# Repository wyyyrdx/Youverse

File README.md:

# 🌌 Youverse

> **You are here. Your habits shape the possibilities.**

### Built for Reverie Hacks 2026

Youverse is a behavioral simulation platform that explores how your current habits and environment can influence different possible versions of your future self.

Instead of telling you what your future will be, Youverse helps you understand how your **current state can shape future possibilities**.

[🎥 Watch the Demo](https://youtu.be/ZdHFRG2crXw?si=tzGFYWxcKCb7MCAu)

---

## 📖 Contents

- [🧠 The Idea](#-the-idea)
- [✨ Why Youverse?](#-why-youverse)
- [🔮 How It Works](#-how-it-works)
- [🪐 The Future Selves](#-the-future-selves)
- [🎮 What-If Simulation](#-what-if-simulation)
- [🏗️ System Architecture](#️-system-architecture)
- [🛠️ Tech Stack](#️-tech-stack)
- [📁 Repository Structure](#-repository-structure)
- [🚀 How to run the project](#-How-to-run-the-project)
- [📊 Data Flow](#-data-flow)
- [🔬 Scientific Honesty](#-scientific-honesty)
- [🧪 Current Status](#-current-status)
- [🌱 Future Vision](#-future-vision)
- [👥 Team](#-team)

---

## 🧠 The Idea

We often think about the future as a single destination.

But the future is shaped by what we repeatedly do today.

Youverse turns that idea into an interactive experience.

A physical device collects environmental and behavioral signals. These signals are transformed into behavioral features and processed by a lightweight modeling system. The result is a distribution across several possible **Future Selves**.

The user can then explore a **What-If scenario** by changing a hypothetical habit and observing how the modeled distribution changes.

> **Youverse does not predict your actual future. It helps you explore how your present behavior can influence different modeled possibilities.**

---

## ✨ Why Youverse?

Most productivity and habit-tracking tools tell you what you are doing.

Youverse asks a different question:

> **"If I keep going like this, what kind of person could I be moving toward?"**

And more importantly:

> **"What happens if I change something today?"**

The goal is not to create a deterministic prediction.

The goal is to make the connection between **present behavior and future possibilities** tangible, visual, and interactive.

---

## 🔮 How It Works

```text
Physical Environment
        ↓
ESP32 + Sensors
        ↓
Behavioral Signals
        ↓
Feature Extraction
        ↓
Behavioral Modeling
        ↓
Future-State Distribution
        ↓
Interactive What-If Simulation
        ↓
3D Future Selves Visualization
```

### 1. Sense

An ESP32-based device collects environmental and behavioral signals using sensors such as:

- Light
- Motion
- Temperature
- Other environmental signals

### 2. Interpret

The collected signals are transformed into engineered behavioral features such as activity, stability, quietness, and other relevant indicators.

### 3. Model

A lightweight behavioral scoring system maps these features to several modeled future states.

### 4. Visualize

The results are presented as an interactive visualization where multiple possible Future Selves coexist.

### 5. Explore

The user can modify a hypothetical behavioral input through the **What-If Engine** and immediately see how the modeled distribution changes.

---

## 🪐 The Future Selves

Youverse represents the future as a set of possibilities rather than a single prediction.

Each Future Self represents a modeled behavioral direction based on the current signals and assumptions.

| Future Self | Represents |
|---|---|
| 🎯 Focused You | Strong concentration and consistency |
| 🔥 Consistent You | Stable routines and sustained behavior |
| 🎨 Creative You | Higher exploration and creative activity |
| ⚡ Active You | Increased physical activity and engagement |
| 🌫️ Burned-Out You | Patterns associated with low stability or sustained strain |

These states are part of the simulation and should not be interpreted as psychological or medical diagnoses.

---

## 🎮 What-If Simulation

One of the core ideas behind Youverse is that **small changes can change the modeled possibilities**.

The user can modify a hypothetical behavioral input and observe the result.

```text
Current State
     ↓
"What if I become more consistent?"
     ↓
Recalculate
     ↓
New Future-State Distribution
```

This turns the experience from simply observing data into exploring possible consequences of changing behavior.

---

## 🏗️ System Architecture

```text
ESP32 Sensors
      │
      │ WiFi / HTTPS
      ▼
FastAPI Backend
      │
      ├── Data Processing
      ├── Feature Extraction
      └── Behavioral Modeling
      │
      ▼
Supabase / PostgreSQL
      │
      ▼
Future-State Distribution
      │
      ▼
What-If Simulation
      │
      ▼
React + TypeScript
      │
      ▼
Three.js / React Three Fiber
      │
      ▼
Interactive 3D Visualization
```

---

## 🛠️ Tech Stack

| Layer | Technology |
|---|---|
| Hardware | ESP32-WROOM-32 |
| Sensors | DHT11/22, LDR, PIR, potentiometer |
| Display | SSD1306 OLED |
| PCB Design | KiCad |
| Firmware | C++ / Arduino |
| Hardware Simulation | Wokwi |
| Backend | Python / FastAPI |
| Database | Supabase / PostgreSQL |
| AI / ML | Python / Engineered Behavioral Features / Weighted Scoring |
| Frontend | React / TypeScript |
| Styling | Tailwind CSS |
| 3D Visualization | Three.js / React Three Fiber |
| Backend Hosting | Railway |

---

## 📁 Repository Structure

```text
Youverse/
├── frontend/
├── backend/
├── hardware/ ---> checkout DRC (hardware/pcb) & ERC (hardware/schematic)
├── firmware/
├── docs/ ---> tech report & flowchart
├── .gitignore
└── README.md
└── LICENSE
```

---

## 🚀 How to run the project

### Prerequisites

- Python 3.10+
- Node.js 18+
- npm
- Supabase account
- Arduino CLI or Arduino IDE
- Wokwi account for hardware simulation

### Clone the Repository

```bash
git clone https://github.com/wyyyrdx/Youverse.git
cd Youverse
```

### Backend

```bash
cd backend
pip install -r requirements.txt
```

Create a `.env` file based on `.env.example`:

```env
SUPABASE_URL=your_supabase_url
SUPABASE_KEY=your_supabase_key
```

Run the backend:

```bash
uvicorn app.main:app --reload --port 8000
```

API documentation:

```text
http://localhost:8000/docs
```

### Frontend

```bash
cd frontend
npm install
npm run dev
```

### Hardware

The firmware and hardware simulation are located in:

```text
firmware/
hardware/simulation/wokwi/
```

You can use the Wokwi simulation without physical hardware.

For the complete hardware setup, wiring, PCB files, and firmware instructions, see the corresponding directories in the repository.

---

## 📊 Data Flow

```text
Sensor Readings
      ↓
Behavioral Features
      ↓
Model Scoring
      ↓
Future States
      ↓
What-If Scenario
      ↓
Updated Distribution
```

The backend stores the relevant data and provides the API used by the frontend.

---

## 🔬 Scientific Honesty

Youverse uses quantum-inspired language and visualization as a conceptual metaphor.

It does **not** perform real quantum computing, and the Future Selves shown by the system are not guaranteed predictions.

The probabilities displayed by the application are **modeled likelihoods generated by the behavioral simulation system**.

They should be interpreted as an exploration of possible outcomes under the model's assumptions, not as facts about a person's actual future.

The system is also not intended to provide medical, psychological, or diagnostic conclusions.

---

## 🧪 Current Status

### Implemented

- [x] ESP32 sensor architecture
- [x] Hardware simulation
- [x] Behavioral feature extraction
- [x] Backend API
- [x] Database integration
- [x] Future-state modeling
- [x] What-If simulation
- [x] Interactive frontend
- [x] 3D Future Selves visualization

### Current Prototype Note

Youverse is currently a functional prototype that combines an interactive frontend, behavioral simulation, backend services, and a simulated ESP32-based hardware layer.

The current experience demonstrates the complete concept and data flow, while parts of the physical sensing pipeline are simulated rather than continuously collected from a deployed physical device.

The Future Selves and their probabilities are generated by the project's behavioral model. They represent modeled possibilities based on the available inputs and should not be interpreted as predictions of a person's actual future.

The next stage is to connect the physical hardware directly to the live pipeline, allowing real-world environmental and behavioral signals to continuously influence the user's modeled possibility space.

---

## 🌱 Future Vision

Youverse is currently a prototype exploring the relationship between present behavior and possible future states.

In future versions, the system could become a more complete personal reflection platform by combining richer behavioral signals, improved modeling, personalized feedback, and a more capable physical device.

The long-term vision is simple:

> **Make the future feel less like something that happens to you and more like something your present actions can influence.**

---

## 👥 Team

Built by:

- **[Wyyyrdx]** — [Hardware&Firmware engineer]
- **[Salmansanusisani]** — [Ai/Ml engineer]
- **[Awaisranahmad]** — [Backend engineer]

### 🏆 Hackathon

Built for **Reverie Hacks 2026**

[🔗 View our Devpost submission](https://devpost.com/software/youverse?ref_content=my-projects-tab&ref_feature=my_projects)

---

## 📄 License

This project is licensed under the MIT License.

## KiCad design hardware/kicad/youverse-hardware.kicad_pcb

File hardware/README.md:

# Hardware - Youverse

## Overview

An ESP32-based sensor node collects environmental/behavioral signals (light, temperature, humidity, motion, noise) as proxies for behavioral patterns, displays them live on an onboard OLED screen, and streams them to the backend over WiFi/HTTPS every 5 seconds. Currently simulated via Wokwi; physical assembly is planned post-hackathon once components are sourced.

## Folder Structure

- `bom/` — Bill of Materials
- `kicad/` — KiCad schematic + PCB project files
- `schematics/` — Exported schematic (PDF)
- `pcb/` — PCB layout, DRC report, renders
- `simulation/wokwi/` — Wokwi simulation files (diagram.json, wokwi.toml)
- `wiring/` — Pin connection reference

## Components & Pin Mapping

| Component | Signal | ESP32 GPIO (Physical Pin) |
|---|---|---|
| DHT11/22 | Temperature + Humidity | GPIO4 (Pin 26) |
| LDR (Photoresistor) | Light (voltage divider) | GPIO34 (Pin 6) |
| PIR Motion Sensor | Motion | GPIO27 (Pin 12) |
| Potentiometer (10kΩ) | Noise (manual input) | GPIO35 (Pin 7) |
| SSD1306 OLED (I2C) | Local display | GPIO21 SDA (Pin 33), GPIO22 SCL (Pin 36) |

Full connection details in `wiring/connections.md`. Full component list with quantities in `bom/BOM.md`.

## Design Process

1. **Schematic** (KiCad Eeschema) — all components placed and wired according to the pin mapping above. ESP32-WROOM-32 powered via AP2112K-3.3 LDO regulator from USB Micro-B, with decoupling capacitors and an EN pull-up resistor per standard ESP32 reference design.
2. **ERC (Electrical Rules Check)** — passed clean. Remaining notices are expected unused pins (SPI-flash internal pins, USB data lines not used since only power is drawn from USB) — documented, not functional issues.
3. **PCB Layout** — footprints assigned to every symbol, components placed in logical zones (Power / MCU / Sensors / Display) around the ESP32, all antenna keep-out zone requirements respected (no traces or components placed over the ESP32's onboard antenna area).
4. **DRC (Design Rules Check)** — passed with 0 real violations after fixing drill-size and zone-fill issues. Power distribution uses filled copper zones for +3V3 and GND to simplify routing and improve reliability. Remaining notices (USB shield pin, zone self-reference) documented as known non-issues.

## Status

✅ Schematic complete and ERC-clean
✅ PCB routed and DRC-clean
✅ Sensor Data Contract agreed with Backend team
✅ Full end-to-end pipeline verified live (sensors → OLED → WiFi → backend → database)
✅ Real sensor data collected from a live device session and used for AI model calibration
⏳ Physical enclosure design - in progress (Tinkercad concept, cosmic/orb-shaped device)
⏳ Physical assembly - planned post-hackathon once components are sourced

## Known Non-Issues (Documented)

- **USB Shield pin (J1)** - intentionally unconnected; no functional impact.
- **+3V3 zone self-reference warnings** - persist even after zone deletion/recreation; a known KiCad zone-fill quirk. Every +3V3 pad has been individually verified as correctly connected to the zone.

## Physical Enclosure (In Progress)

The device's outer shell is designed to match the project's visual identity a "miniature quantum planet / superposition orb" concept (cosmic, pixel-art inspired), modeled in Tinkercad. Full physical assembly is planned post-hackathon.

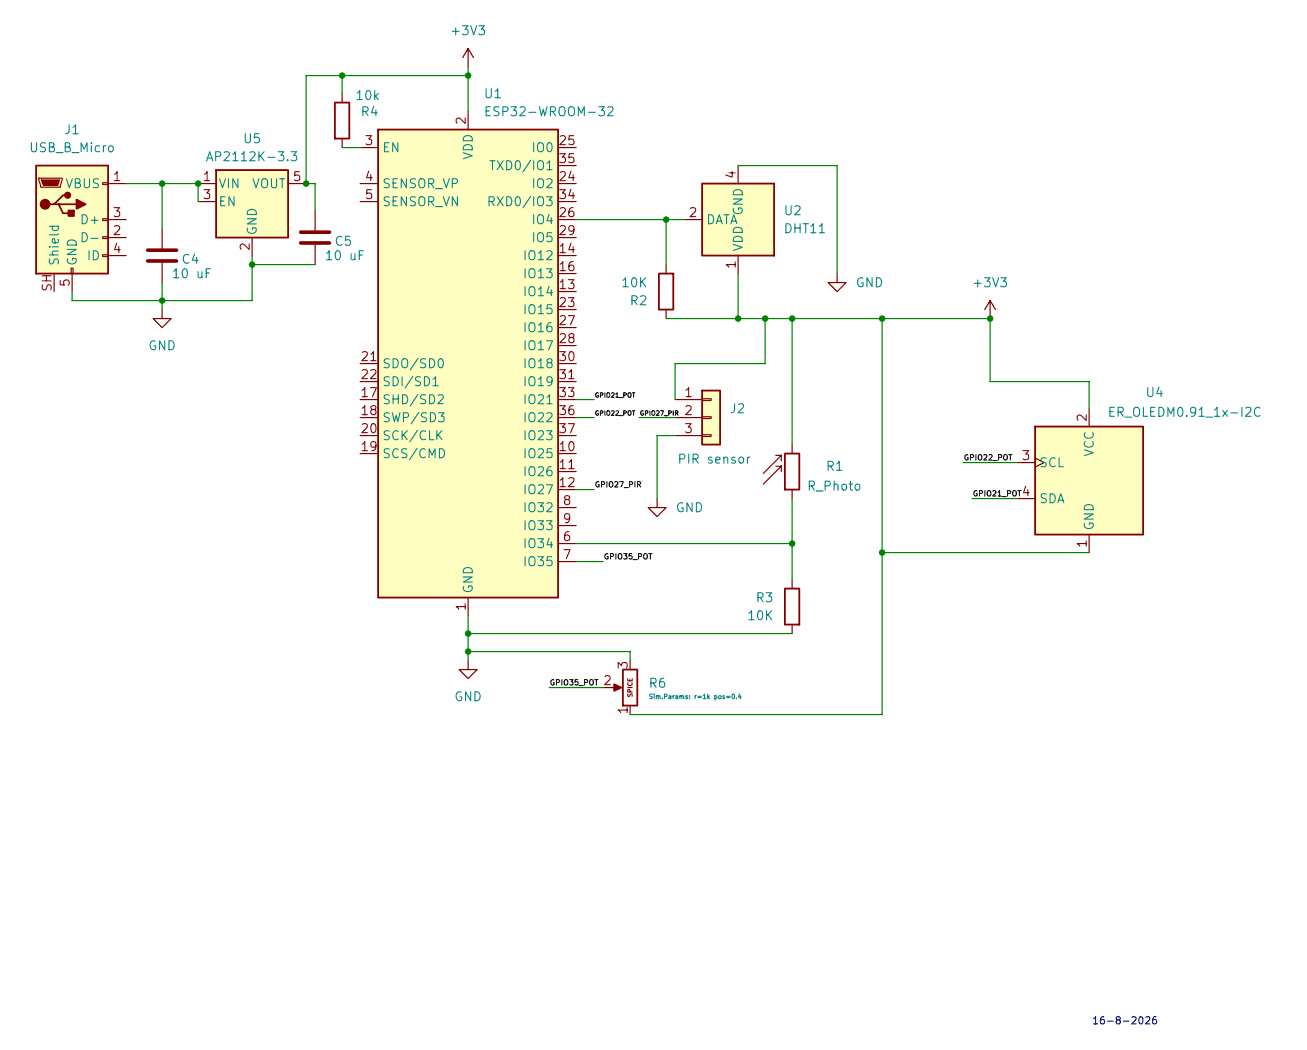
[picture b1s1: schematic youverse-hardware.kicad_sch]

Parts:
C4, C5: 10 uF; CP_Radial_D5.0mm_P2.00mm
J1: USB_B_Micro; USB_Micro-B_Molex-105017-0001
J2: PIR sensor; PinHeader_1x03_P2.54mm_Vertical
R1: R_Photo; R_Axial_DIN0207_L6.3mm_D2.5mm_P10.16mm_Horizontal
R2, R3: 10K; R_Axial_DIN0207_L6.3mm_D2.5mm_P10.16mm_Horizontal
R4: 10k; R_Axial_DIN0207_L6.3mm_D2.5mm_P10.16mm_Horizontal
R6: Potentiometer; Potentiometer_Bourns_3296W_Vertical
U1: ESP32-WROOM-32
U2: DHT11; Aosong_DHT11_5.5x12.0_P2.54mm
U4: ER_OLEDM0.91_1x-I2C
U5: AP2112K-3.3; SOT-23-5

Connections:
+3V3: C5.2, J2.1, R1.2, R2.1, R4.1, R6.1, U1.2 (VDD), U2.1 (VDD), U4.1 (GND), U4.2 (VCC), U5.5 (VOUT)
/GPIO21_POT: U1.33 (IO21), U4.4 (SDA)
/GPIO22_POT: U1.36 (IO22), U4.3 (SCL)
/GPIO27_PIR: J2.2, U1.12 (IO27)
/GPIO35_POT: R6.2, U1.7 (IO35)
GND: C4.1, C5.1, J1.5 (GND), J2.3, R3.2, R6.3, U1.1 (GND), U1.15 (GND), U1.38 (GND), U1.39 (GND), U2.4 (GND), U5.2 (GND)
unnamed: C4.2, J1.1 (VBUS), U5.1 (VIN), U5.3 (EN)
unnamed: R4.2, U1.3 (EN)
unnamed: R2.2, U1.26 (IO4), U2.2 (DATA)
unnamed: R1.1, R3.1, U1.6 (IO34)

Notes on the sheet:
16-8-2026

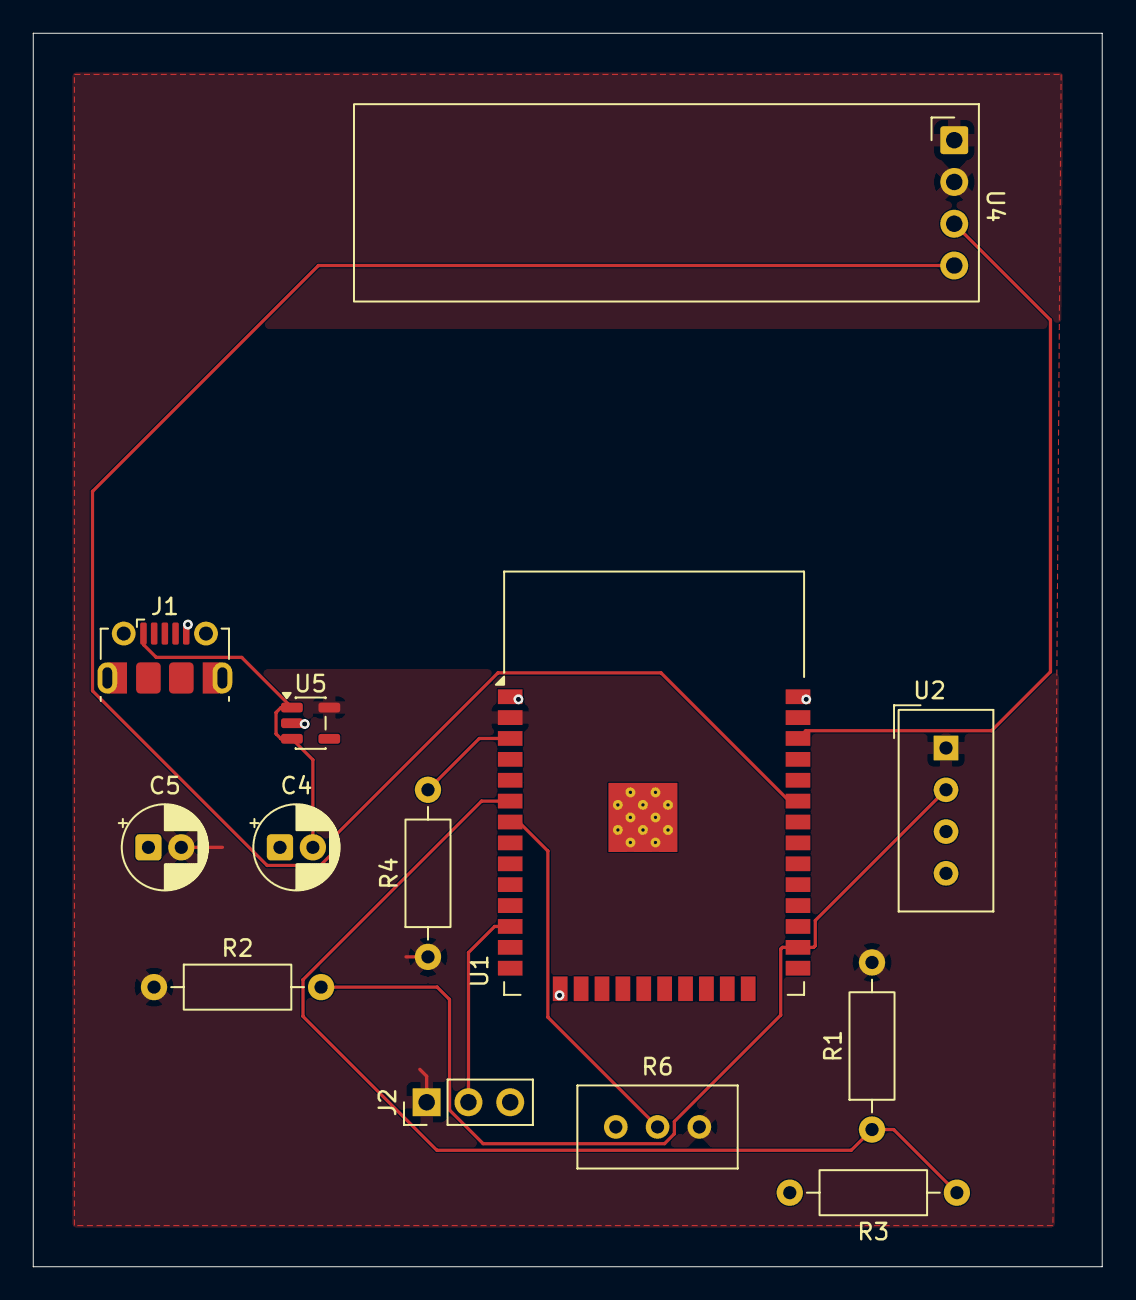
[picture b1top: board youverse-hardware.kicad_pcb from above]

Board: 2 copper layers, 65.0 x 75.0 mm, 13 parts (0 on the bottom side), 10 nets.
